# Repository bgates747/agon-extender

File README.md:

# Agon Extender

Agon Extender adds an ESP32-P4 coprocessor to an Agon computer. **Extended
Display Processor (EDP)** runs on P4; **Extender MOS (EMOS)** replaces MOS on the
eZ80 and owns display routing, keyboard admission and Extender transports.

This is a working development project, not a general ready-to-install release.
The tree includes retained experiments and diagnostic targets. A source checkout,
a successful compile and a deployed/qualified combination are different things.

## Start here

The [Extender handbook](docs/README.md) is the current documentation entry point.

1. **Using an existing installation:** [operator and external-agent entry point](docs/using-extender.md).
2. **Transferring files:** [mainboard SD guide](docs/mainboard-sd.md), including the
   foreground `EMOS sdserve` EMOSlet and paired `--fast` option.
3. **Building:** [component build guide](docs/building.md). Select the native
   `p4-console` profile explicitly; the retained PlatformIO files are historical
   rollback material.
   The accepted r55 console was reconstructed from maintained source; select
   exact approved bytes through [production](production/README.md), not Git HEAD.
4. **Unfinished work:** [TODO](TODO.md). Task records preserve dated evidence;
   they are not automatically current operating instructions.

## Capabilities and limits

Current handbook review: **27 September 2026** (documentation/source inspection). Results apply to the
recorded builds and bench, not every Agon/P4 combination.

| Capability | Current status and authority |
|---|---|
| Legacy / Exclusive Compatible (ExCom) display routing | EMOS selects mainboard VDP or EDP. Retained VDP rendering and browser output work; compatibility and performance limits remain. [Architecture](docs/architecture.md), [bug register](docs/firmware-bugs.md). |
| Physical, browser and agent keyboard input | P4 USB input, explicit browser capture and paced host automation are implemented. All require EMOS to have admitted Extender input. Physical input takes priority; browser capture overrides automation. [Keyboard guide](docs/remote-keyboard.md). |
| Browser video and observation | P4 serves the page and final rendered pixels, with full-frame RLE2 by default. Browser output can slow gameplay; presented fps is not application-loop or native-rendering throughput. [Video contract](docs/protocols/browser-video.md). |
| Agon mainboard SD | Foreground `EMOS sdserve [--fast] /` supports listing, reads and recoverable staged replacement. Normal mode verifies whole files; fast mode omits those verification passes. EMOSlet installation and latest scoped physical checks: [operating guide](docs/mainboard-sd.md). It does not run alongside a game. |
| Remote reset | An optional Pi-hosted bridge pulses the Agon's reset circuit; the browser button uses that bridge. This is not P4-native reset or power cycling. [Reset guide](docs/bench-reset.md). |
| P4-local SD | Development candidate provides CLI/HTTP file and directory management; bounded r57 hardware checks recorded, outside selected production v0.1.0. [P4 SD guide](docs/p4-sd.md). Current bench firmware must be checked separately. |
| Future / deferred | Audio: [PORT-004](docs/tasks/PORT-004.md). Parallel transport, MicroPython and physical video outputs remain separate work; see [TODO](TODO.md). |

Network services use plain HTTP/WebSocket on a trusted LAN, without
authentication. The SD root passed to `sdserve` bounds access; `/` exposes the
whole mainboard card. The SD wire API does not execute programs. Agent keyboard
control can issue MOS commands only after its input path is already admitted.

The current physical reference is **Agon Light 2 + Olimex ESP32-P4-DevKit Rev D1**.
The [r03 UART harness](hardware/designs/light2-harness-r03/README.md) and its
USB addition are not a complete qualification of every as-built circuit.
The planned **ESP32-P4-PC** has a separate [reference library](docs/hardware/esp32-p4-pc/README.md)
with manuals, schematics, provenance and upstream example-clone instructions.
Do not treat the planned board as the installed DevKit.

## Source ownership and further reading

| Component / subject | Entry point |
|---|---|
| Integrated P4 console | [native profile authority](vdp/build/p4-profiles.json), [native builder](scripts/build_p4.py), [p4_console.cpp](vdp/video/extender/boot/p4_console.cpp) |
| EDP / adapted VDP | [vdp/video/extender](vdp/video/extender/), [vdp/video](vdp/video/), [retained libraries](vdp/vendor/) |
| EMOS and SD listener | [agon-emos](https://github.com/bgates747/agon-emos), including `src/` and `projects/sdserve/` |
| Host SD client | [scripts/sdcard.py](scripts/sdcard.py) |
| Embedded browser assets | [web component](vdp/video/extender/web/README.md); no separate npm build |
| Design and responsibility | [architecture](docs/architecture.md), [ownership](OWNERSHIP.md), [protocols](docs/protocols/) |
| Qualification and known faults | [qualification index](docs/qualification/README.md), [firmware bugs](docs/firmware-bugs.md), [publication review](docs/public-release-readiness.md) |
| Evidence and research | [task conventions](docs/tasks/README.md), [TRS-OS community guide](docs/tasks/TRS-80-002/COMMUNITY-GUIDE.md), [hardware-free samples](docs/tasks/TRS-80-002/bin/README.md) |

## License and upstream work

Agon Extender is distributed under **GPL-3.0-only**, except where individual
files or third-party components carry their own compatible license notices.
See [LICENSE](LICENSE) for the full text and [LICENSING.md](LICENSING.md) for
the licensing and attribution policy.

The port builds on the [official Agon VDP](https://github.com/AgonPlatform/agon-vdp)
and FabGL/vdp-gl. Original MIT and GPL-family notices and upstream attribution
remain applicable to their respective sources.

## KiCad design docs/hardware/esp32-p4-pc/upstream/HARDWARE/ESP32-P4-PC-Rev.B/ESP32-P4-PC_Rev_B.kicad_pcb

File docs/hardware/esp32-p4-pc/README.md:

# Olimex ESP32-P4-PC reference library

Local, provenance-recorded copies of Olimex's board documentation are stored
here so research does not require rediscovering web links. The official upstream
repository is also cloned separately for complete software examples and design
sources. This is reference material, not Extender firmware or board qualification.

## Start here

## Current Rev C authority — 2026-10-02

The Author confirms receipt of an **Olimex ESP32-P4-PC Rev C**, replacing the
DevKit as the project target. The authoritative manufacturer reference is the
[official Olimex repository](https://github.com/OLIMEX/ESP32-P4-PC), with the
local read-only checkout verified at commit
`04032d68e5c727870f9d40beb9e37b7ab3a66916`.
Use its `HARDWARE/ESP32-P4-PC-Rev.C/` schematic, design and BOM,
`HARDWARE/Hardware-revision-changes.txt`, and `DOCUMENTS/` manual for Rev C
research. The machine-local checkout location is recorded in
`agents/p4pc-reference/LOCAL.md`.

The vendored files and `PROVENANCE.json` below remain the historical Rev B
snapshot at `89a7b96e2ec4c3f28b55d768dfda3ba8a86846bd`; their hashes and
provenance have not been relabelled as Rev C. They are not the current board's
documentation authority. Receipt does not establish integration or qualification.
The Pi 5 now hosts development and the P4-PC bench; standalone P4-PC tests
precede Agon reconnection. Current topology and remaining identity/wiring
verification boundaries are recorded in `HARDWARE.local.md`.

## Rev C shared GPIO/SD supply

**Mandatory P4-PC startup requirement: enable and retain LDO4 at 3.3 V before
using transport GPIO46. This applies even with no SD card.** Select
`--board p4-pc` when building for Rev C; `--board p4-devkit` selects different
pins and power ownership. The builder defaults to DevKit and does not detect
the attached board. See [board build selection](../../building.md#board-selection-and-compile-time-pin-mapping).

GPIO39–48 use VDDPST_5, which the Rev C PCB connects to ESP_LDO_VO4.
Transport D7/GPIO46 therefore needs LDO4 even when no P4-local SD card is used.
The maintained P4-PC console initializes and retains a fixed 3.3V supply before
console GPIO setup. SDMMC uses four data lines at its default 20MHz/3.3V and
cannot acquire an adjustable owner, switch the shared bank to 1.8V or turn it
off after mount failure. DevKit transport D7/GPIO9 uses a different I/O bank;
its existing SD-only supply lifecycle remains unchanged.

The manufacturer PCB source at the Rev C commit above and Espressif's
[chip v1.3 datasheet](https://documentation.espressif.com/esp32-p4-chip-revision-v1.3_datasheet_en.html)
establish the connection. The [direction-isolation results](../../tasks/PORT-008/DIRECTION-ISOLATION-R01.md)
record the independently compared physical transfers and current qualification
boundary. This correction does not establish successful P4-PC SD mounting.

Rev C also has a separate card-supply switch: GPIO45 is `SD1_PWR_EN`, driving
FET1's active-low gate to connect `VDD_SD`. The manufacturer production-test
configuration at `04032d68` selects GPIO45=0 and100ms stabilization before SDMMC
initialization. The maintained PC board profile now records these values and
the local SD driver enables the switch once before mounting; it retains LDO4
and never formats or power-cycles after failure. The earlier omission left the
card supply uncontrolled despite a powered I/O bank. Hardware confirmation belongs
to [REMOTE-009](../../tasks/REMOTE-009.md). Its corrected application is now
independently flash-verified; the original card timeout persisted during that
installation. The Author subsequently reseated the loose card and original r25
mounts successfully. Physical seating explains that failure; this does not
demonstrate a faulty card or the power-enable omission as its cause. Broader
P4-local file operation and coexistence qualification remain separate.

Espressif's [hardware design guide](https://docs.espressif.com/projects/esp-hardware-design-guidelines/en/latest/esp32p4/schematic-checklist-esp32p4.html)
documents GPIO46's VDD_IO_5 bank and the software-controlled LDO output, which
defaults to off. No matching issue appears in the
[chip v1.3 errata](https://docs.espressif.com/projects/esp-chip-errata/en/latest/esp32p4/_tags/v1-3.html)
checked on 2026-10-11. This was our board integration defect; the regulator is
operating according to its documented initialization requirement.

## Retained Rev B snapshot

| Resource | Local copy |
|---|---|
| User manual | [PDF](upstream/DOCUMENTS/ESP32-P4-PC-user-manual.pdf) · [searchable text](text/ESP32-P4-PC-user-manual.txt) · [editable upstream original](upstream/DOCUMENTS/ESP32-P4-PC-user-manual.odt) |
| Rev.B schematic | [PDF](upstream/HARDWARE/ESP32-P4-PC-Rev.B/ESP32-P4-PC_Rev_B.pdf) · [searchable text](text/ESP32-P4-PC_Rev_B.txt) |
| Hardware design and BOM | [Rev.B directory](upstream/HARDWARE/ESP32-P4-PC-Rev.B/) |
| Board photographs | [Documents directory](upstream/DOCUMENTS/) |
| ESP-IDF production test instructions | [README](upstream/SOFTWARE/ESP-IDF/p4_production_test/README.md) |
| Arduino MIPI display demo instructions | [README](upstream/SOFTWARE/Arduino/ESP32-P4-PC-MIPI-LCD-Arduino/README.md) |
| EU conformity declaration | [PDF](website/EU-DOC-ESP32-P4-PC.pdf) |
| UKCA declaration | [PDF](website/UKCA-ESP32-P4-PC.pdf) |
| Product-page snapshot | [Archived HTML](website/product-page.html); external page assets were not mirrored |
| Exact origins, licenses and hashes | [PROVENANCE.json](PROVENANCE.json) · [upstream licensing statement](upstream/README.md#licensee) |

[HDMI driver research](HDMI-DRIVERS.md) identifies the existing Espressif driver
and Olimex production-test integration.

## Complete software and hardware repository

[Official OLIMEX/ESP32-P4-PC repository](https://github.com/OLIMEX/ESP32-P4-PC),
pinned documentation snapshot:
`89a7b96e2ec4c3f28b55d768dfda3ba8a86846bd`.

A clean reference clone has been installed on the Linux development host. Its
clickable local checkout/examples links are in the ignored
`agents/p4pc-reference/LOCAL.md`, and HARDWARE.local.md points there. Absolute
machine paths intentionally stay out of tracked documentation. In the standard
Agon workspace layout the checkout is the `ESP32-P4-PC` sibling of `mystuff`.

Full source includes ESP-IDF production tests, Arduino examples, vendored BSP
code, KiCad files and 3D component models. Upstream examples are references;
do not infer compatibility with this project's pinned toolchain or flash them
onto the working bench merely because they are present. Keep the upstream
checkout clean; experiments belong in project-owned working directories.

## Provenance and scope

Unmodified board files are copied under `upstream/`, preserving original paths.
Included: all upstream DOCUMENTS, board hardware files except the bulky generic
3D package library, and board-specific software documentation. Full dependency
and other-board documentation remains in the complete clone rather than being
presented here as P4-PC documentation. Product HTML and the two directly linked
regulatory PDFs are stored under `website/` with retrieval metadata.

`text/` contains marked pdftotext derivatives for searching. Consult original
PDFs for pinouts, electrical diagrams and visual layout. Each original and
extract has a SHA-256 record; upstream files also have commit-pinned source URLs.
This snapshot describes the upstream Rev.B files; the received board is Rev C.

Olimex states documentation CC BY-SA4.0, hardware CERN-OHL-S2.0 and software MIT;
retain upstream notices and individual dependency licenses. Imported originals
have not been edited. Extracts only change representation; attribution and
applicable document terms remain. Website documents retain their own notices.

To refresh deliberately: fetch/review upstream changes, select a commit, replace
copies from that revision, refresh website sources and text derivatives, and
update/verify provenance hashes. Do not silently mix changing upstream files
into this pinned snapshot. Board integration remains in
[P4PC-001](../../tasks/P4PC-001.md).

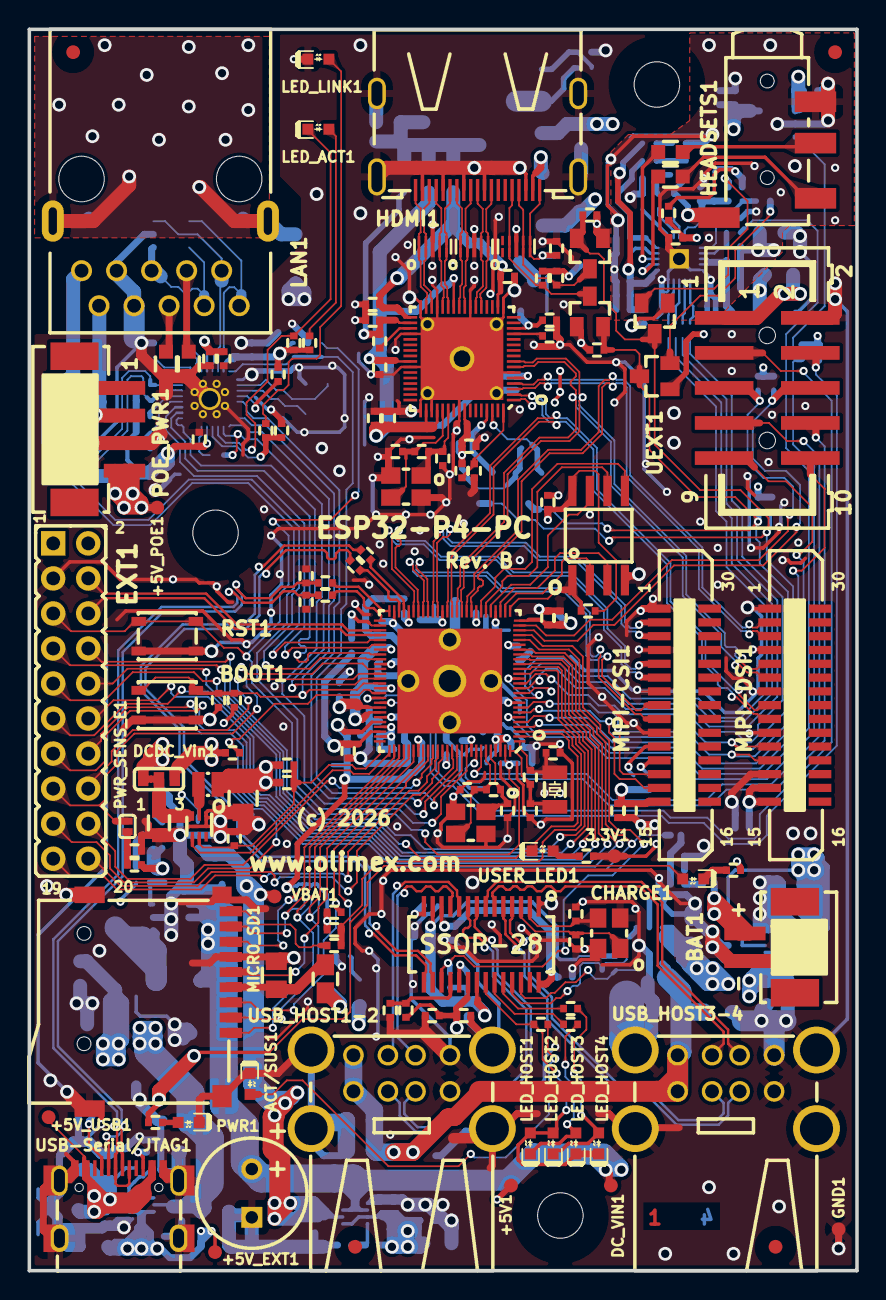
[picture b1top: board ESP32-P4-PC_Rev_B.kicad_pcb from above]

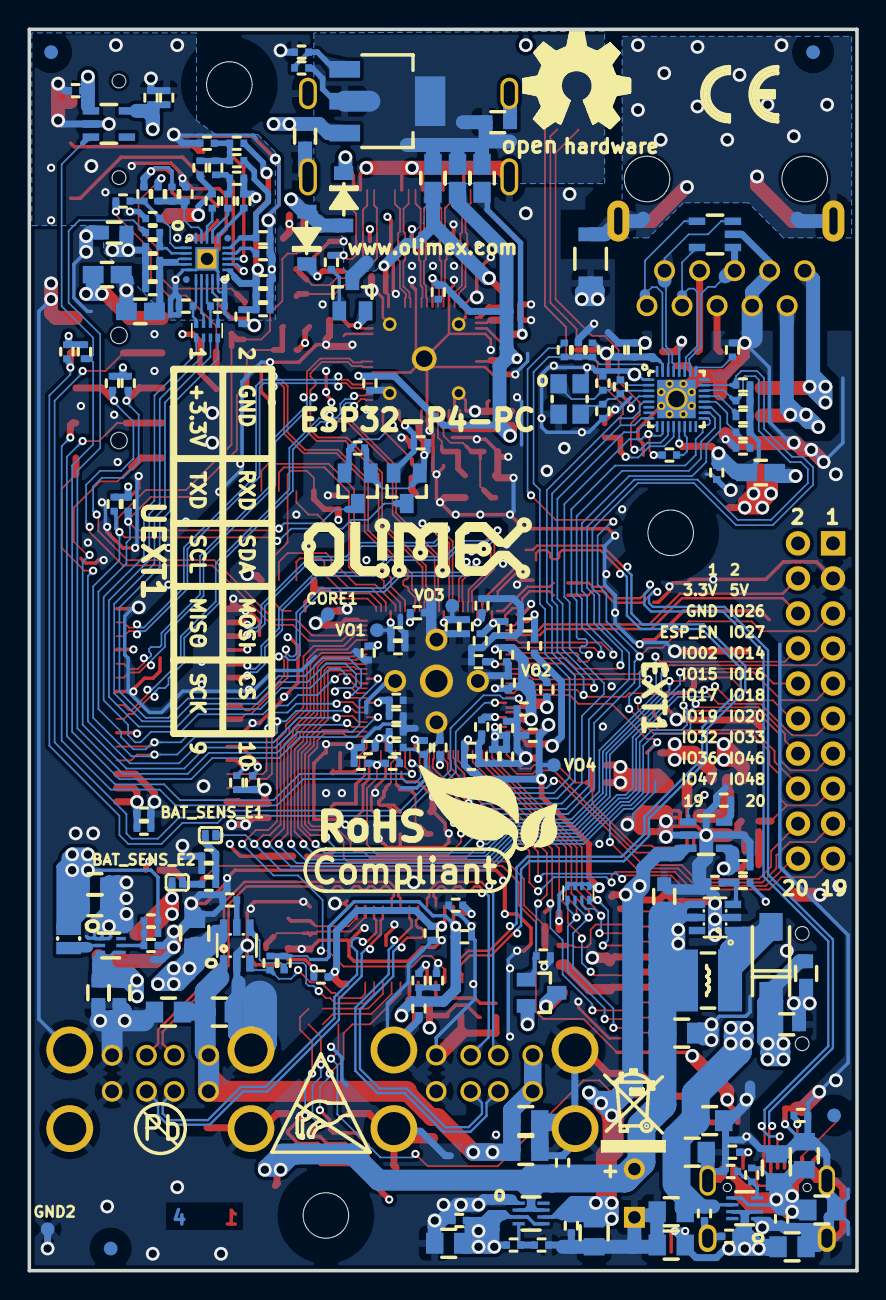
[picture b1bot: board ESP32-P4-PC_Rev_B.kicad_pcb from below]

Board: 4 copper layers, 60.0 x 90.0 mm, 344 parts (204 on the bottom side), 223 nets.

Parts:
3.3V1: TESTPAD; TESTPAD_40-ROUND
+5V1, +5V_EXT1, +5V_POE1, +5V_USB1: TESTPAD; TESTPAD_40-ROUND
ACT/SUS1: LED/RED/0603; LED_0603_KA
BAT1: PH2.0-2AT; PH2.0-2AT(BAT)
BAT_SENS_E1, BAT_SENS_E2: Opened; SJ_1_SMALLER
BOOT1: YTS-A016-X
C1, C2, C44, C45: 22pF/50V/5%/C0G/C0402; C_0402_5MIL_DWS
C3, C6, C18, C20, C22, C29, C41, C50, C56, C67, C68, C70, C76, C82, C99: 10uF/6.3V/20%/X5R/C0402; C_0402_5MIL_DWS
C4, C5, C7, C9, C11, C12, C19, C21, C23, C30, C31, C32, C38, C40, C42, C43, C46, C47, C49, C51, C52, C53, C54, C57, C69, C71, C85, C87, C91, C94, C95, C96, C101, C105, C106, C107, C108, C109, C111, C112, C115, C119, C120, C121, C128, C131: 100nF/10V/20%/X5R/C0402; C_0402_5MIL_DWS
C8, C10, C36, C39, C48, C55, C58, C61, C84, C86, C88, C97, C98, C100, C104, C126: 1uF/6.3V/10%/X5R/C0402; C_0402_5MIL_DWS
C13: 4.7uF/X5R/20%/10V/C0402; C_0402_5MIL_DWS
C14, C65, C74, C92, C93, C118, C129, C130, C132, C133, C134, C136: 47uF/6.3V/20%/X5R/C0805; C_0805_5MIL_DWS
C15, C16: 100nF/50V/20%/Y5V/C0603; C_0603_5MIL_DWS
C17: 1nF/2000V/10%/X7R/C1206; C_1206_5MIL_DWS_ISO
C24, C25, C79, C80, C81, C113, C114: 27pF/50V/5%/C0G/C0402; C_0402_5MIL_DWS
C26, C83: NA(10uF/6.3V/20%/X5R/C0402); C_0402_5MIL_DWS
C27, C28: 150pF/50V/2%/NP0/C0402; C_0402_5MIL_DWS
C33, C60: NA(100nF/10V/20%/X5R/C0402); C_0402_5MIL_DWS
C34, C64, C122: NA(22uF/6.3V/20%/X5R/C0603); C_0603_5MIL_DWS
C35, C37, C63, C66, C75, C102, C103, C123, C124: 22uF/6.3V/20%/X5R/C0603; C_0603_5MIL_DWS
C59, C62: NA(120pF/50V/5%/C0G/C0402); C_0402_5MIL_DWS
C72, C73: NA(27pF/50V/5%/C0G/C0402); C_0402_5MIL_DWS
C77, C78: 20pF/50V/5%/NP0/C0402; C_0402_5MIL_DWS
C89, C90, C116, C125, C127, C135: NA(47uF/6.3V/20%/X5R/C0805); C_0805_5MIL_DWS
C110: 2.2nF/50V/10%/X7R/C0402; C_0402_5MIL_DWS
C117: 1000uF/10V/20%; CPOL-RM3.5mm_8.0x11.5mm_PTH
CHARGE1: LED/Yellow/0603; LED_0603_KA
CORE1: TESTPAD; TESTPAD_40-ROUND
D2, D3: 1N5819S4(SOD123); SOD-123_1C-2A_KA
D4: 1N5822/SS34/SMA; SMA-KA
DCDC_Vin1: Closed(1-2); SJ_2_SMALL_12_TIED
DC_VIN1: TESTPAD; TESTPAD_40-ROUND
EXT1: NA(HN2x10); HN2x10
FET1: IRLML6402(SOT-23); SOT23
FET3, FET4, FET5, FET6, FET7, FET8: BSS138(SOT-23); SOT23
FID1, FID3, FID5, FID7: Fiducial; Fiducial1x3
FID2, FID4, FID6, FID8: Fiducial; Fiducial1x3_Paste
GND1, GND2: TESTPAD; TESTPAD_40-ROUND
HDMI1: HDMI-SWM-19; HDMI-SWM-19_Paste
HEADSETS1: PJ-320D
L1, L2, L5, L6, L7, L8: 600OHM/2A/UPZ2012E-601-2R0TF/0805; L_0805_5MIL_DWS
L3, L4: 1.0uH/4.2A/DCR=35mR/20%/2.00x1.60x1.00mm/L2016(PI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; L_2016_MM
L9: NA(600OHM/2A/UPZ2012E-601-2R0TF/0805); L_0805_5MIL_DWS
L11: 4.7uH/2.33A/DCR=70mR/20%/CD43(NRS4018T4R7MDGJ); CD42(43)
LAN1: RJP-003TC1(LPJ4112CNL)
LED_ACT1: LED/Yellow/0603; LED_0603_KA
LED_HOST1, LED_HOST2, LED_HOST3, LED_HOST4: LED/GREEN/0603; LED_0603_KA
LED_LINK1: LED/GREEN/0603; LED_0603_KA
Logo_OLIMEX_TB: Logo_OLIMEX_TB
MH1, MH2, MH3: Mounting_Hole_NPTH; Mounting_Hole_Drill-3.3mm_Clerance-7mm
MICRO_SD1: TFC-WPAPR-08-LF; TFC-WPAPR-08
MIPI-CSI1: FPA-VZA2-15-LF; TE_1-1734248-5
MIPI-DSI1: FPA-VZA2-15-LF; TE_1-1734248-5
POE_PWR1: PH2.0-4AT; PH2.0-4PLB
PWR1: LED/RED/0603; LED_0603_KA
PWR_SENS_E1: Opened; SJ_1_SMALLER
Q1: Q32.768kHz/12.5pF/2P/SMD1206; CM7V-T1A(Crystal_Package-1206_3.20x1.50x0.65mm)
Q2, Q6: Q25MHz/18pF/30ppm/4P/3.2x2.5mm(ABM8-25.000MHZ-D2Y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; TSX-3.2x2.5mm_GND(3)
Q3: Q40.000MHz/12pF/10ppm/4P/3.2x2.5x0.70mm(Harmony_E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; TSX-3.2x2.5mm_GND(3)
Q4: Q12MHz/18pF/30ppm/4P/3.2x2.5mm(ABM8-12.000MHZ-D2Y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; TSX-3.2x2.5mm_GND(3)
Q5: BC817-40; SOT23
R1, R2: 4.02k/1%/R0402; R_0402_5MIL_DWS
R3, R27, R41, R42, R43, R48, R54, R55, R64, R66, R67, R68, R70, R83, R85, R86, R102: 10k/R0402; R_0402_5MIL_DWS
R4, R8, R9, R39, R56, R57, R61, R62, R72, R73, R74, R80, R82, R84, R88, R91, R92, R93: 2.2k/R0402; R_0402_5MIL_DWS
R5, R6: 5.1k/1%/R0402; R_0402_5MIL_DWS
R7, R10, R11, R12, R21, R22, R33, R37, R49, R69: 4.7k/R0402; R_0402_5MIL_DWS
R13: 10M/R0402; R_0402_5MIL_DWS
R14, R15, R16, R25, R26, R38: 22R/R0402; R_0402_5MIL_DWS
R17: 6.19k/1%/R0402; R_0402_5MIL_DWS
R18, R28: NA(10k/R0402); R_0402_5MIL_DWS
R19, R32, R63, R81: NA/R0402; R_0402_5MIL_DWS
R20: NA(10M/R0402); R_0402_5MIL_DWS
R23: NA(4.7k/R0402); R_0402_5MIL_DWS
R24, R105: 24.9k/1%/R0402; R_0402_5MIL_DWS
R29, R30: NA(2.2k/R0402); R_0402_5MIL_DWS
R31: 0R/R0603; R_0603_5MIL_DWS
R34, R35: 1.5k/R0402; R_0402_5MIL_DWS
R36: 220k/R0402; R_0402_5MIL_DWS
R40: NA(0R/R0402); R_0402_5MIL_DWS
R44: 30.1k/1%/R0402; R_0402_5MIL_DWS
R45: 6.49k/1%/R0402; R_0402_5MIL_DWS
R46, R47: 10.5k/1%/R0402; R_0402_5MIL_DWS
R50: 110R/1%/R0402; R_0402_5MIL_DWS
R51: 49.9k/1%/R0402; R_0402_5MIL_DWS
R52: 240R/1%/R0402; R_0402_5MIL_DWS
R53: 2.7k/1%/R0402; R_0402_5MIL_DWS
R58, R59, R60: 33R/R0402; R_0402_5MIL_DWS
R65, R71, R75: 100k/R0402; R_0402_5MIL_DWS
R76: 6.04k/1%/R0402; R_0402_5MIL_DWS
R77: 10R/R0402; R_0402_5MIL_DWS
R78: NA(200R/R0402); R_0402_5MIL_DWS
R79: 200R/R0402; R_0402_5MIL_DWS
R87: 1M/R0402; R_0402_5MIL_DWS
R89, R103: 6.81k/1%/R0402; R_0402_5MIL_DWS
R90, R94, R96: 470k/R0402; R_0402_5MIL_DWS
R95: 8.25k/1%/R0402; R_0402_5MIL_DWS
R98: 1.05k/1%/R0402; R_0402_5MIL_DWS
RM1: RMAT_(4x0402)_4.7k; RA0805_(4X0402)_xx_BIGGEROUTPADS
RM2: RA0805_(4X0402)_33R; RA0805_(4X0402)_xx_BIGGEROUTPADS
RST1: YTS-A016-X
Sign_Antistatic: Sign_Antistatic
Sign_CE: CE_Sign
Sign_OSHW_8x8: Sign_OSHW_8x8
Sign_PB-Free: Sign_PB-Free
Sign_RecycleBin_1: Sign_RecycleBin_1
Sign_RoHS_1: Sign_RoHS_1
TVS1: ESDS314DBVR(SOT-23-5); SOT-23-5
U1: ESP32-P4NRWxx(QFN104); QFN104_10mm×10mm_Pitch_0.35mm
U2: IP101GRR(32-PIN_QFN); QFN32_EP(33)_4.00x4.00x0.80mm_Pitch_0.40mm
U3: W25Q128JVSIQ(16MB); SO-8_208mil
U4, U5: TPS62A02ADRLR(SOT-563-6); SOT-563-6
U6: CH217K(SOT23-6L); SOT23-6
U7: FE1.1s(SSOP-28); SSOP28_10x4mm_Pitch_0.64mm
U8: ES8311(QFN-20); QFN-20_EP(21)_3x3x0.6mm_Pitch_0.4mm
U9, U10, U11: NA(RCLAMP0524P(SLP2510P8)); SLP2510P8_TEST
U12: LT8912B(QFN64); QFN64_7.5x7.5mm_Pitch_0.4mm
U13, U16: TPS2116; SOT-5X3
U14: MT3608(SOT23-6); SOT23-6
U15: TP4054-42-SOT25-R(SOT23-5); SOT-23-5
UEXT1: P-B-V-10-LF; GBH-254-SMT-10
USB-Serial/JTAG1: USB-C-16P-F(A40-00119-A52-12); USB2.0_TYPE-C(A40-00119-A52-12)_Paste
USB_HOST1-2, USB_HOST3-4: USBB1-FRWH-4A(USB-Ax2); USB_TWO_LEVEL
USER_LED1: LED/GREEN/0603; LED_0603_KA
VBAT1: TESTPAD; TESTPAD_40-ROUND
VO1, VO2, VO3, VO4: TESTPAD; TESTPAD_40-ROUND
VR1: LD1117AG-AD-AA3-A-R; SOT223
VR2: AP1231-3.3V(SOT23-5); SOT-23-5

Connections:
+1V8: C39.2, C54.2, C55.2, U1.59 (VDDPST), U1.67 (VDDPST), U1.72 (VFB2/VO2), VO2.1 (Pad)
+2.5V: C10.1, C11.1, C58.2, U1.41 (VDD_MIPI_DPHY), U1.73 (VFB3/VO3), VO3.1 (Pad)
+3.3V: 3.3V1.1 (Pad), C3.1, C4.1, C5.2, C12.1, C13.1, C29.1, C30.1, C32.2, C41.2, C42.2, C43.2, C46.2, C50.2, C51.2, C53.2, C56.1, C57.1, C59.2, C63.1, C64.1, C66.1, DCDC_Vin1.3, EXT1.1, FET1.2, FET7.1 (G), FET8.1 (G), L2.1, L3.2, L9.1, MIPI-CSI1.15, MIPI-DSI1.14, MIPI-DSI1.15, R4.1, R27.1, R28.1, R29.1, R30.1, R33.2, R41.1, R42.1, R43.1, R44.2, R49.1, R83.1, R86.1, R92.2, R93.2, U1.9 (VDDPST_1), U1.21 (VDDPST_2), U1.51 (VCCA), U1.62 (VDDPST_4), U1.75 (VDDPST_LDO), U1.77 (VDDPST_DCDC), U1.96 (VDDPST_6), U1.101 (VDDA), U1.102 (VBAT), UEXT1.1, VR1.3 (IN)
+3.3VA: C82.1, FET3.1 (G), FET4.1 (G), L5.1, L9.2, R56.2, R57.2, R63.2, R68.1, R77.1, VR2.5 (VOUT)
+5V: +5V1.1 (Pad), C67.1, C74.1, C76.1, C91.2, C122.1, C123.1, D2.2 (A), D3.2 (A), D4.1 (K), EXT1.2, R69.2, R95.1, U6.6 (VIN), U7.20 (V5), VR2.1 (VIN)
+5VP: +5V_POE1.1 (Pad), C120.2, C134.2, C135.2, C136.2, POE_PWR1.4, U13.6 (VIN2)
+5V_EXT: +5V_EXT1.1 (Pad), C31.2, C118.2, C125.1, C126.1, C130.1, C131.2, CHARGE1.2 (A), R36.1, R39.2, R105.2, U13.2 (VOUT), U13.7 (VOUT), U15.4 (VCC), U16.3 (VIN1), U16.5 (MODE)
+5V_USB: +5V_USB1.1 (Pad), C119.2, C127.2, C132.2, C133.2, R24.2, U13.3 (VIN1), U13.5 (MODE), USB-Serial/JTAG1.A4 (VBUS), USB-Serial/JTAG1.A9 (VBUS), USB-Serial/JTAG1.B4 (VBUS), USB-Serial/JTAG1.B9 (VBUS)
/3.3V_PHY: C20.1, C21.1, C22.1, C23.1, L2.2, R7.2, R8.2, R18.1, R21.1, R22.1, R34.1, R35.1, R37.1, U2.13 (VDD_IO), U2.31 (AVDD33)
/50MHz_CLKO: R38.2, U2.14 (RXCLK/50M_CLKO)
/+5V_HDMI: D3.1 (K), HDMI1.18
/+5V_USB_HOST: C89.2, C90.2, C92.2, C93.2, U6.1 (VOUT), USB_HOST1-2.1.1, USB_HOST1-2.2.1, USB_HOST3-4.1.1, USB_HOST3-4.2.1
/ADCVREF: C86.1, R79.2, U8.15 (ADCVREF)
/CSI_CLKN: MIPI-CSI1.8, U1.45 (CSI_CLKN)
/CSI_CLKP: MIPI-CSI1.9, U1.44 (CSI_CLKP)
/CSI_DATA0N: MIPI-CSI1.2, U1.42 (CSI_DATAN0)
/CSI_DATA0P: MIPI-CSI1.3, U1.43 (CSI_DATAP0)
/CSI_DATA1N: MIPI-CSI1.5, U1.46 (CSI_DATAN1)
/CSI_DATA1P: MIPI-CSI1.6, U1.47 (CSI_DATAP1)
/CSI_IO0\Reset: MIPI-CSI1.11, R27.2
/CSI_IO1\Strobe: MIPI-CSI1.12, R28.2
/DCDC_VIN: C34.1, C37.1, C116.2, C117.1 (+), C124.1, C128.2, DCDC_Vin1.1, DC_VIN1.1 (Pad), L11.2, U4.3 (VIN), U4.4 (EN), U14.4 (EN), U14.5 (IN), U16.2 (VOUT), U16.7 (VOUT)
/DCDC_Vin: C35.1, DCDC_Vin1.2, U5.3 (VIN)
/DSI_CLKN: MIPI-DSI1.5, U1.37 (DSI_CLKN), U12.8 (MIPIRX_CKN)
/DSI_CLKP: MIPI-DSI1.6, U1.38 (DSI_CLKP), U12.7 (MIPIRX_CKP)
/DSI_DATA0N: MIPI-DSI1.8, U1.40 (DSI_DATAN0), U12.2 (MIPIRX0_DN)
/DSI_DATA0P: MIPI-DSI1.9, U1.39 (DSI_DATAP0), U12.1 (MIPIRX0_DP)
/DSI_DATA1N: MIPI-DSI1.2, U1.36 (DSI_DATAN1), U12.4 (MIPIRX1_DN)
/DSI_DATA1P: MIPI-DSI1.3, U1.35 (DSI_DATAP1), U12.3 (MIPIRX1_DP)
/EN_DCDC: U1.79 (EN_DCDC), U5.4 (EN)
/ESP_EN: C40.2, EXT1.5, R19.1, R41.2, RST1.1, U1.103 (CHIP_PU)
/ESP_LDO_VO1: C8.2, C9.2, C36.1, C38.2, R48.1, U1.30 (VDDPST_3), U1.71 (VFB1/VO1), U3.8 (VCC), VO1.1 (Pad)
/ESP_LDO_VO4: C48.1, C49.1, C61.2, R11.1, R12.1, RM1.1.2, RM1.2.2, RM1.3.2, RM1.4.2, U1.74 (VFB4/VO4), U1.85 (VDDPST_5), VO4.1 (Pad)
/FB_DCDC: C62.1, R46.1, R47.1, U1.78 (FB_DCDC), U5.5 (FB)
/FLASH_CK: U1.32 (FLASH_CK), U3.6 (CLK)
/FLASH_CS: R48.2, U1.27 (FLASH_CS), U3.1 (#CS)
/FLASH_D: U1.33 (FLASH_D), U3.5 (DI(IO0))
/FLASH_HOLD: U1.31 (FLASH_HOLD), U3.7 (#HOLD(IO3))
/FLASH_Q: U1.28 (FLASH_Q), U3.2 (DO(IO1))
/FLASH_WP: U1.29 (FLASH_WP), U3.3 (#WP(IO2))
/GPIO2\User_Led: EXT1.7, U1.2 (GPIO2/TOUCH_0/MTCK), USER_LED1.1 (K)
/GPIO3\SD_DET: R12.2, R16.1, U1.3 (GPIO3/TOUCH_1/MTDI)
/GPIO4\SPI_SCK(CLK): U1.4 (GPIO4/TOUCH_2/MTMS), UEXT1.9
/GPIO5\SPI_CSn(CS#): U1.5 (GPIO5/TOUCH_3/MTDO), UEXT1.10
/GPIO6\CODEC_PWR_DIS#: R49.2, U1.6 (GPIO6/TOUCH_4/GPSPI_SPI2_HOLD), VR2.3 (CE)
/GPIO7\I2C_SDA: FET3.3 (D), FET6.3 (D), FET7.2 (S), MIPI-CSI1.14, MIPI-DSI1.12, R30.2, R83.2, U1.7 (GPIO7/TOUCH_5/GPSPI_SPI2_CS)
/GPIO8\I2C_SCL: FET4.3 (D), FET5.3 (D), FET8.2 (S), MIPI-CSI1.13, MIPI-DSI1.11, R29.2, R86.2, U1.8 (GPIO8/TOUCH_6/GPSPI_SPI2_D/UART0_RTS)
/GPIO9\I2S_DSDIN: RM2.4.1, U1.10 (GPIO9/TOUCH_7/GPSPI_SPI2_CK/UART0_CTS)
/GPIO10\I2S_LRCK: RM2.3.1, U1.11 (GPIO10/TOUCH_8/GPSPI_SPI2_Q/UART1_TXD)
/GPIO11\I2S_ASDOUT: RM2.2.1, U1.12 (GPIO11/TOUCH_9/GPSPI_SPI2_WP/UART1_RTD)
/GPIO12\I2S_SCLK: RM2.1.1, U1.13 (GPIO12/TOUCH_10/UART1_RTS)
/GPIO13\I2S_MCLK: R60.2, U1.14 (GPIO13/TOUCH_11/UART0_CTS)
/GPIO14: EXT1.8, U1.15 (GPIO14/TOUCH_12/LP_UART_TXD)
/GPIO15: EXT1.9, U1.16 (GPIO15/TOUCH_13/LP_UART_RXD)
/GPIO16: EXT1.10, U1.17 (GPIO16/ADC0)
/GPIO17: EXT1.11, U1.18 (GPIO17/ADC1)
/GPIO18: EXT1.12, U1.19 (GPIO18/ADC2)
/GPIO19: EXT1.13, U1.20 (GPIO19/ADC3)
/GPIO20/BAT_SENSE: BAT_SENS_E1.2, EXT1.14, U1.22 (GPIO20/ADC4)
/GPIO21/HUB_RST#: R54.2, U1.23 (GPIO21/ADC5), U7.17 (XRSTJ)
/GPIO22/I2C_SDA2: R93.1, U1.24 (GPIO22/ADC6/DBG_PSRAM_CK), UEXT1.6
/GPIO23/I2C_SCL2: R92.1, U1.25 (GPIO23/ADC7/50MHz_ref_clk_out/DBG_PSRAM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), UEXT1.5
/GPIO26/USB1P1_1N: EXT1.4, U1.55 (GPIO26/USB1P1_N1)
/GPIO27/USB1P1_1P: EXT1.6, U1.56 (GPIO27/USB1P1_P1)
/GPIO32/EXT_PWR_SEN: EXT1.15, PWR_SENS_E1.2, U1.63 (GPIO32/I3CMST_SCL/GPSPI_SPI2_HOLD/EMAC_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)
/GPIO33: EXT1.16, U1.64 (GPIO33/I3CMST_SDA/GPSPI_SPI2_WP/EMAC_PH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)
/GPIO34\RMII_TXD0: U1.65 (GPIO34/GPSPI_SPI2_IO4/EMAC_PHY_TXD0/DBG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), U2.9 (TXD0)
/GPIO35\RMII_TXD1: BOOT1.1, C60.1, R43.2, U1.66 (GPIO35/GPSPI_SPI2_IO5/EMAC_PHY_TXD1/DBG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), U2.8 (TXD1)
/GPIO36: EXT1.17, R42.2, U1.68 (GPIO36/GPSPI_SPI2_IO6/EMAC_PHY_TXER/DBG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)
/GPIO46: EXT1.18, U1.88 (GPIO46/SD1_DATA5/EMAC_PHY_RXD0/DBG_PSRA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)
/GPIO47: EXT1.19, U1.89 (GPIO47/SD1_DATA6/EMAC_PHY_RXD1/DBG_PSRA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)
/GPIO48: EXT1.20, U1.90 (GPIO48/SD1_DATA7/EMAC_PHY_RXER)
/GPIO53\SPI_TX(MOSI): U1.97 (GPIO53/ADC12/EMAC_PHY_RXD1/DBG_FLASH_CK), UEXT1.8
/GPIO54\SPI_RX(MISO): U1.98 (GPIO54/ADC13/EMAC_PHY_RXER/DBG_FLASH_D), UEXT1.7
/HP-L: C103.1, HEADSETS1.4
/HP-R: C102.1, HEADSETS1.3
/HPD_DET: HDMI1.19, R71.2, R75.1, U11.5 (IN4), U11.6 (OUT4)
/HSCL: FET8.3 (D), HDMI1.15, R88.2, U11.2 (IN2), U11.9 (OUT2)
/HSDA: FET7.3 (D), HDMI1.16, R84.2, U11.4 (IN3), U11.7 (OUT3)
/HUB_DRV: LED_HOST1.2 (A), LED_HOST2.2 (A), LED_HOST3.1 (K), LED_HOST4.1 (K), R74.1, U7.22 (DRV)
/HUB_LED1: R72.1, U7.23 (LED1/SCL)
/HUB_LED2: R73.1, U7.24 (LED2)
/LAN_Shield: C17.2, LAN1.0 (Shield)
/LED0\PHY_AD0: LED_ACT1.1 (K), R7.1, U2.11 (LED0/PHY_AD0)
/LED3\PHY_AD3: R9.2, R10.2, U2.12 (LED3/PHY_AD3)
/LT8912_SCL: FET5.2 (S), R61.2, U12.62 (S_SCL)
/LT8912_SDA: FET6.2 (S), R62.2, U12.61 (S_SDA)
/LX2: D4.2 (A), L11.1, U14.1 (LX)
/MDC: R34.2, U1.61 (GPIO31/GPSPI_SPI2_Q/EMAC_PHY_RXER/DBG_P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), U2.22 (MDC)
/MDIO: R35.2, U1.95 (GPIO52/ADC11/EMAC_PHY_RXD0/DBG_FLASH_HO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), U2.23 (MDIO)
/MICN: C97.1, R80.2, R81.2
/MICP: C98.1, HEADSETS1.1, R82.2
/OVCUR#: R67.1, U6.3 (FLAG#), U7.26 (OVCJ)
/PHY_RSTN: C26.1, R18.2, R19.2, U1.94 (GPIO51/ADC10/EMAC_PHY_RXDV/DBG_FLASH_WP), U2.32 (RESET_N)
/PW+: LAN1.9 (PW+), POE_PWR1.2
/PW-: LAN1.10 (PW-), POE_PWR1.1
/PWREN#: R66.1, U6.4 (EN#), U7.25 (PWRJ)
/RD+: LAN1.3 (RD+), TVS1.5 (I/O4), U2.27 (MDI_RP)
/RD-: LAN1.6 (RD-), TVS1.1 (I/O1), U2.26 (MDI_RN)
/RMII_CLK: R38.1, U1.93 (GPIO50/ADC9/EMAC_RMII_CLK/DBG_FLASH_Q), U2.10 (TXCLK/50M_CLKI)
/RMII_RXD0: U1.58 (GPIO29/GPSPI_SPI2_D/EMAC_PHY_RXD0/DBG_P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), U2.18 (RXD0)
/RMII_RXD1: U1.60 (GPIO30/GPSPI_SPI2_CK/EMAC_PHY_RXD1/DBG_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), U2.17 (RXD1)
/RMII_RXDV: U1.57 (GPIO28/GPSPI_SPI2_CS/EMAC_PHY_RXDV/DBG_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), U2.19 (RXDV/CRS_DV/FX_HEN)
/RMII_TXEN: U1.92 (GPIO49/ADC8/EMAC_PHY_TXEN/DBG_FLASH_CS), U2.5 (TXEN)
/RXER/INTR_32: R37.2, U2.21 (RXER/INTR_32)
/SD1_CLK: MICRO_SD1.5 (CLK/SCLK), U1.84 (GPIO43/SD1_CLK/EMAC_PHY_TXER/DBG_PSRAM_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)
/SD1_CMD: MICRO_SD1.3 (CMD/DI), R11.2, U1.86 (GPIO44/SD1_CMD/EMAC_RMII_CLK/DBG_PSRAM_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)
/SD1_D0: MICRO_SD1.7 (DAT0/DO), RM1.4.1, U1.80 (GPIO39/SD1_CDATA0/reference_clock_of_50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)
/SD1_D1: MICRO_SD1.8 (DAT1/RES), RM1.3.1, U1.81 (GPIO40/SD1_CDATA1/EMAC_PHY_TXEN/DBG_PSR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)
/SD1_D2: MICRO_SD1.1 (DAT2/RES), RM1.2.1, U1.82 (GPIO41/SD1_CDATA2/EMAC_PHY_TXD0/DBG_PSR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)
/SD1_D3: MICRO_SD1.2 (CD/DAT3/CS), RM1.1.1, U1.83 (GPIO42/SD1_CDATA3/EMAC_PHY_TXD1/DBG_PSR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)
/SD1_PWR_EN: FET1.1, R3.2, U1.87 (GPIO45/SD1_DATA4/EMAC_PHY_RXDV/DBG_PSRA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)
/SD1_VDD: C14.1, L1.2, MICRO_SD1.4 (VDD)
/SW1: L3.1, U4.2 (SW)
/TD+: LAN1.1 (TD+), TVS1.4 (I/O3), U2.30 (MDI_TP)
/TD-: LAN1.2 (TD-), TVS1.3 (I/O2), U2.29 (MDI_TN)
/TX0_DN: HDMI1.9, U10.2 (IN2), U10.9 (OUT2), U12.24 (HDMITX0_DN)
/TX0_DP: HDMI1.7, U10.1 (IN1), U10.10 (OUT1), U12.25 (HDMITX0_DP)
/TX1_DN: HDMI1.6, U9.5 (IN4), U9.6 (OUT4), U12.27 (HDMITX1_DN)
/TX1_DP: HDMI1.4, U9.4 (IN3), U9.7 (OUT3), U12.28 (HDMITX1_DP)
/TX2_DN: HDMI1.3, U9.2 (IN2), U9.9 (OUT2), U12.30 (HDMITX2_DN)
/TX2_DP: HDMI1.1, U9.1 (IN1), U9.10 (OUT1), U12.31 (HDMITX2_DP)
/TX_CKN: HDMI1.12, U10.5 (IN4), U10.6 (OUT4), U12.21 (HDMITX_CKN)
/TX_CKP: HDMI1.10, U10.4 (IN3), U10.7 (OUT3), U12.22 (HDMITX_CKP)
/TX_HPD: Q5.2 (E), R65.1, U12.14 (HPD_CBUS)
/UART0_RX: R33.1, U1.70 (GPIO38/UART0_RXD/GPSPI_SPI2_DQS), UEXT1.4
/UART0_TX: U1.69 (GPIO37/UART0_TXD/GPSPI_SPI2_IO7), UEXT1.3
/USB1P1_0+: R25.2, U1.53 (GPIO25/USB1P1_P0)
/USB1P1_0-: R26.2, U1.52 (GPIO24/USB1P1_N0)
/USB1P1_0N: C27.1, R26.1, USB-Serial/JTAG1.A7 (DN1), USB-Serial/JTAG1.B7 (DN2)
/USB1P1_0P: C28.1, R25.1, USB-Serial/JTAG1.A6 (DP1), USB-Serial/JTAG1.B6 (DP2)
/USB_D1+: U7.11 (DP1), USB_HOST1-2.1.3
/USB_D1-: U7.10 (DM1), USB_HOST1-2.1.2
/USB_D2+: U7.9 (DP2), USB_HOST1-2.2.3
/USB_D2-: U7.8 (DM2), USB_HOST1-2.2.2
/USB_D3+: U7.7 (DP3), USB_HOST3-4.1.3
/USB_D3-: U7.6 (DM3), USB_HOST3-4.1.2
/USB_D4+: U7.5 (DP4), USB_HOST3-4.2.3
/USB_D4-: U7.4 (DM4), USB_HOST3-4.2.2
/USB_D+: R15.1, U1.50 (DP)
/USB_D-: R14.1, U1.49 (DM)
/USB_DN: R14.2, U7.15 (DMU)
/USB_DP: R15.2, U7.16 (DPU)
/VD18_O: C70.1, C71.1, U7.12 (VD18_O), U7.28 (VD18)
/VD33_O: C68.1, C69.1, R54.1, R55.1, R66.2, R67.2, U7.13 (VD33), U7.21 (VD33_O)
/VDD_SD: FET1.3, L1.1
GND: ACT/SUS1.1 (K), BAT1.2, BOOT1.2, C1.1, C2.1, C3.2, C4.2, C5.1, C6.2, C7.2, C8.1, C9.1, C10.2, C11.2, C12.2, C13.2, C14.2, C15.1, C16.1, C17.1, C18.2, C19.2, C20.2, C21.2, C22.2, C23.2, C24.1, C25.1, C26.2, C27.2, C28.2, C29.2, C30.2, C31.1, C32.1, C33.1, C34.2, C35.2, C36.2, C37.2, C38.1, C39.1, C40.1, C41.1, C42.1, C43.1, C44.1, C45.1, C46.1, C47.1, C48.2, C49.2, C50.1, C51.1, C52.1, C53.1, C54.1, C55.1, C56.2, C57.2, C58.1, C60.2, C61.1, C63.2, C64.2, C65.2, C66.2, C67.2, C68.2, C69.2, C70.2, C71.2, C72.2, C73.2, C74.2, C75.2, C89.1, C90.1, C91.1, C92.1, C93.1, C94.2, C95.2, C96.2, C105.1, C106.1, C107.1, C108.1, C109.1, C111.1, C112.1, C113.1, C114.1, C115.1, C116.1, C117.2 (-), C118.1, C119.1, C120.1, C121.1, C122.2, C123.2, C124.2, C125.2, C126.2, C127.1, C128.1, C129.1, C130.2, C131.1, C132.1, C133.1, C134.1, C135.1, C136.1, EXT1.3, GND1.1 (Pad), GND2.1 (Pad), HDMI1.0 (20), HDMI1.2, HDMI1.5, HDMI1.8, HDMI1.11, HDMI1.17, LAN1.7 (GND/NC), LAN1.8 (NC/GND), LED_LINK1.1 (K), MICRO_SD1.6 (VSS), MICRO_SD1.10, MICRO_SD1.11, MICRO_SD1.12, MICRO_SD1.13, MIPI-CSI1.1, MIPI-CSI1.4, MIPI-CSI1.7, MIPI-CSI1.10, MIPI-DSI1.1, MIPI-DSI1.4, MIPI-DSI1.7, MIPI-DSI1.10, MIPI-DSI1.13, POE_PWR1.3, PWR1.1 (K), Q2.3 (case), Q3.3 (case), Q4.3 (case), Q6.3 (case), R1.2, R2.2, R3.1, R5.1, R6.1, R10.1, R17.2, R23.1, R31.1, R45.2, R47.2, R50.1, R51.1, R53.1, R65.2, R70.2, R75.2, R76.1, R89.2, R94.2, R96.2, R98.2, R102.2, R103.2, RST1.2, TVS1.2 (GND), U1.105 (GND), U2.1 (TXER/FXSD), U2.33 (GND), U3.4 (GND), U4.1 (GND), U5.1 (GND), U6.2 (GND), U7.1 (GND), U9.3 (GND), U9.8 (GND), U10.3 (GND), U10.8 (GND), U11.3 (GND), U11.8 (GND), U12.6 (VSSA_MIPIRX), U12.17 (VSS), U12.23 (VSSA_HDMITX), U12.29 (VSSA_HDMITX), U12.32 (VSS), U12.36 (VSSA_HDMIPLL), U12.42 (VSSA_LVDSTX), U12.49 (VSSA_SYSCLK), U12.51 (VSSA_LVDSPLL), U12.56 (VSS), U12.65 (VSS), U13.1 (GND), U14.2 (GND), U15.2 (GND), U16.1 (GND), UEXT1.2, USB-Serial/JTAG1.0 (SHELL), USB-Serial/JTAG1.A1 (GND), USB-Serial/JTAG1.A12 (GND), USB-Serial/JTAG1.B1 (GND), USB-Serial/JTAG1.B12 (GND), USB_HOST1-2.0, USB_HOST1-2.1.4, USB_HOST1-2.2.4, USB_HOST3-4.0, USB_HOST3-4.1.4, USB_HOST3-4.2.4
GNDA: C76.2, C77.2, C78.2, C79.2, C80.2, C81.2, C82.2, C83.2, C84.2, C85.2, C86.2, C87.2, C88.2, C99.2, C100.2, C101.1, C104.2, HEADSETS1.2, R31.2, R64.2, R68.2, R81.1, U8.5 (DGND), U8.10 (AGND), U8.21 (GND_EP), VR2.2 (VSS)
LT8912_VCCA: C94.1, C96.1, C107.2, C108.2, C109.2, L7.2, U12.5 (VCCA_MIPIRX), U12.26 (VCCA_HDMITX), U12.41 (VCCA_LVDSTX), U12.50 (VCCA_SYSCLK), U12.52 (VCCA_LVDSPLL)
LT8912_VCCA_HDMIPLL: C110.1, C111.2, L6.2, U12.34 (VCCA_HDMIPLL)
LT8912_VDD: C95.1, C106.2, C112.2, FET5.1 (G), FET6.1 (G), L8.2, R61.1, R62.1, R85.2, U12.18 (VDD), U12.33 (VDD), U12.57 (VDD)
unnamed: ACT/SUS1.2 (A), R74.2
unnamed: BAT_SENS_E1.1, C115.2, R90.2, R96.1
unnamed: BAT_SENS_E2.1, R90.1
unnamed: C104.1, R78.1, R79.1, R80.1, R82.1
unnamed: CHARGE1.1 (K), R91.1
unnamed: D2.1 (K), R84.1, R88.1
unnamed: FET3.2 (S), R59.2
unnamed: FET4.2 (S), R58.2
unnamed: C16.2, LAN1.5 (RCT)
unnamed: C15.2, LAN1.4 (TCT)
unnamed: LED_ACT1.2 (A), R8.1
unnamed: LED_HOST1.1 (K), LED_HOST3.2 (A), R72.2
unnamed: LED_HOST2.1 (K), LED_HOST4.2 (A), R73.2
unnamed: LED_LINK1.2 (A), R9.1
unnamed: MICRO_SD1.9, R16.2
unnamed: PWR1.2 (A), R39.1
unnamed: PWR_SENS_E1.1, R36.2, R94.1
unnamed: Q5.1 (B), R71.1
unnamed: R2.1, U1.48 (CSI_REXT)
unnamed: R1.1, U1.34 (DSI_REXT)
unnamed: C1.2, Q1.1, R13.1, U1.104 (GPIO0/XTAL_32K_N)
unnamed: C2.2, Q1.2, R13.2, U1.1 (GPIO1/XTAL_32K_P)
unnamed: C33.2, R40.2, U1.54 (NC(VDD_HP_1))
unnamed: C45.2, Q3.2, R32.2, U1.99 (XTAL_N)
unnamed: C44.2, Q3.1, R32.1, U1.100 (XTAL_P)
unnamed: R21.2, U2.4 (COL/RMII)
unnamed: R22.2, R23.2, U2.20 (CRS/LEDMOD)
unnamed: R17.1, U2.25 (ISET)
unnamed: C18.1, C19.1, U2.28 (REGOUT)
unnamed: C24.2, Q2.1, R20.2, U2.2 (X1)
unnamed: C25.2, Q2.2, R20.1, U2.3 (X2)
unnamed: C59.1, R44.1, R45.1, U4.5 (FB)
unnamed: L4.1, U5.2 (SW)
unnamed: R51.2, U6.5 (ISET)
unnamed: R55.2, U7.19 (BUSJ)
unnamed: R53.2, U7.14 (REXT)
unnamed: R69.1, R70.1, U7.18 (VBUSM)
unnamed: C72.1, Q4.1, U7.3 (XI)
unnamed: C73.1, Q4.2, U7.2 (XO)
unnamed: RM2.2.2, U8.7 (ASDOUT)
unnamed: C99.1, C100.1, C101.2, R77.2, R78.2, U8.11 (AVDD)
unnamed: C77.1, R56.1, R58.1, U8.1 (CCLK/SCL)
unnamed: C78.1, R57.1, R59.1, U8.19 (CDATA/SDA)
unnamed: R63.1, R64.1, U8.20 (CE/AD0)
unnamed: C88.1, U8.14 (DACVREF)
unnamed: RM2.4.2, U8.9 (DSDIN)
unnamed: C83.1, C85.1, C87.1, L5.2, U8.3 (PVDD), U8.4 (DVDD)
unnamed: C79.1, RM2.3.2, U8.8 (LRCK)
unnamed: C81.1, R60.1, U8.2 (MCLK)
unnamed: C97.2, U8.17 (MIC1N)
unnamed: C98.2, U8.18 (MIC1P/DMIC_SDA)
unnamed: C102.2, U8.13 (OUTN)
unnamed: C103.2, U8.12 (OUTP)
unnamed: C80.1, RM2.1.2, U8.6 (SCLK/DMIC_SCL)
unnamed: C84.1, U8.16 (VMID)
unnamed: C110.2, U12.35 (LPF)
unnamed: R76.2, U12.13 (R6K)
unnamed: C105.2, R85.1, U12.64 (RESET_N)
unnamed: C114.2, Q6.2, R87.2, U12.53 (XTALI)
unnamed: C113.2, Q6.1, R87.1, U12.54 (XTALO)
unnamed: R24.1, R89.1, U13.4 (PR1)
unnamed: R95.2, R98.1, U14.3 (FB)
unnamed: R91.2, U15.1 (CHRGb)
unnamed: R102.1, U15.5 (PROG)
unnamed: R103.1, R105.1, U16.4 (PR1)
unnamed: R6.2, USB-Serial/JTAG1.A5 (CC1)
unnamed: R5.2, USB-Serial/JTAG1.B5 (CC2)
unnamed: R4.2, USER_LED1.2 (A)
unnamed: R50.2, R52.2, VR1.1 (ADJ/GND)
VBAT: BAT1.1, BAT_SENS_E2.2, C121.2, C129.2, U15.3 (VBAT), U16.6 (VIN2), VBAT1.1 (Pad)
VCC_1.8V: C75.1, L6.1, L7.1, L8.1, Q5.3 (C), R52.1, VR1.2 (OUT)
VDD_CORE: C6.1, C7.1, C47.2, C52.2, C62.2, C65.1, CORE1.1 (Pad), L4.2, R40.1, R46.2, U1.26 (VDD_HP_0), U1.76 (VDD_HP_2), U1.91 (VDD_HP_3)

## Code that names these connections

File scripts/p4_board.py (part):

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admission. Generated outputs are disposable and never an editable authority.

IMPORTANT: --board selects electrical initialization, not just pin numbers.
P4-PC Rev C requires boot-owned 3.3V LDO4 for transport D7/GPIO46 even without
local SD. DevKit D7/GPIO9 does not share that bank. Derive the supply policy
here so a separate optional flag cannot disable the board requirement.
"""
from __future__ import annotations
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    eth = board["ethernet"]
    require(eth["phy"] == "IP101" and type(eth["address"]) is int
            and 0 <= eth["address"] <= 31, "unsupported Ethernet PHY/address")
    require(all(gpio(eth[k]) for k in ("mdc", "mdio", "reset", "clock_input")),
            "invalid Ethernet GPIO")
    # Arduino's P4 EMAC clock selection is fixed to the external clock pad.
    require(eth["clock_input"] == 50, "unsupported P4 RMII clock pad")
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        require(type(power_pin) is int and power_pin == 45
                and type(sd.get("power_on_level")) is int and sd["power_on_level"] == 0
                and type(sd.get("power_settle_ms")) is int and sd["power_settle_ms"] == 100,
                "SD power differs from reviewed Rev C active-low GPIO45 switch")
    else:
        require(power_pin is None, "unreviewed SD power switch")
    usb = board["usb"]
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    require(usb["peripheral_map"] == 0, "only the reviewed HS host selection is supported")
    for key in ("reset_assert_ms", "reset_recovery_ms"):
        require(type(usb[key]) is int and 0 <= usb[key] <= 1000, "invalid USB reset delay")
    peripheral_pins = [eth[k] for k in ("mdc", "mdio", "reset", "clock_input")]
    peripheral_pins += [sd[k] for k in ("clk", "cmd", "d0", "d1", "d2", "d3")]
    if power_pin is not None:
        peripheral_pins.append(power_pin)
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              "UsbPeripheralMap": usb["peripheral_map"]}
    values.update({"Sd" + k.capitalize(): sd[k] for k in ("clk", "cmd", "d0", "d1", "d2", "d3")})
    text += "".join(f"inline constexpr int k{key} = {value};\n" for key, value in values.items())
    # MANDATORY BOARD FORK (FWBUG-014): Rev C powers GPIO39-48, including
    # transport D7/GPIO46, from LDO4. Retain fixed 3.3V from console startup,
    # including absent/failed SD; SD must not switch this bank to 1.8V.
    # DevKit transport pads use independently powered I/O banks. This follows
    # --board automatically; it must not become a separately optional toggle.
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

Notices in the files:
docs/hardware/esp32-p4-pc/upstream/HARDWARE/ESP32-P4-PC-Rev.B/ESP32-P4-PC_Rev_B.kicad_pcb:
(c) 2026
